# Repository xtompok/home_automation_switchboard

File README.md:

# home_automation_switchboard
Board fitting into wall switch, support for 1Wire, quadrature encoder, and much more. RS-485

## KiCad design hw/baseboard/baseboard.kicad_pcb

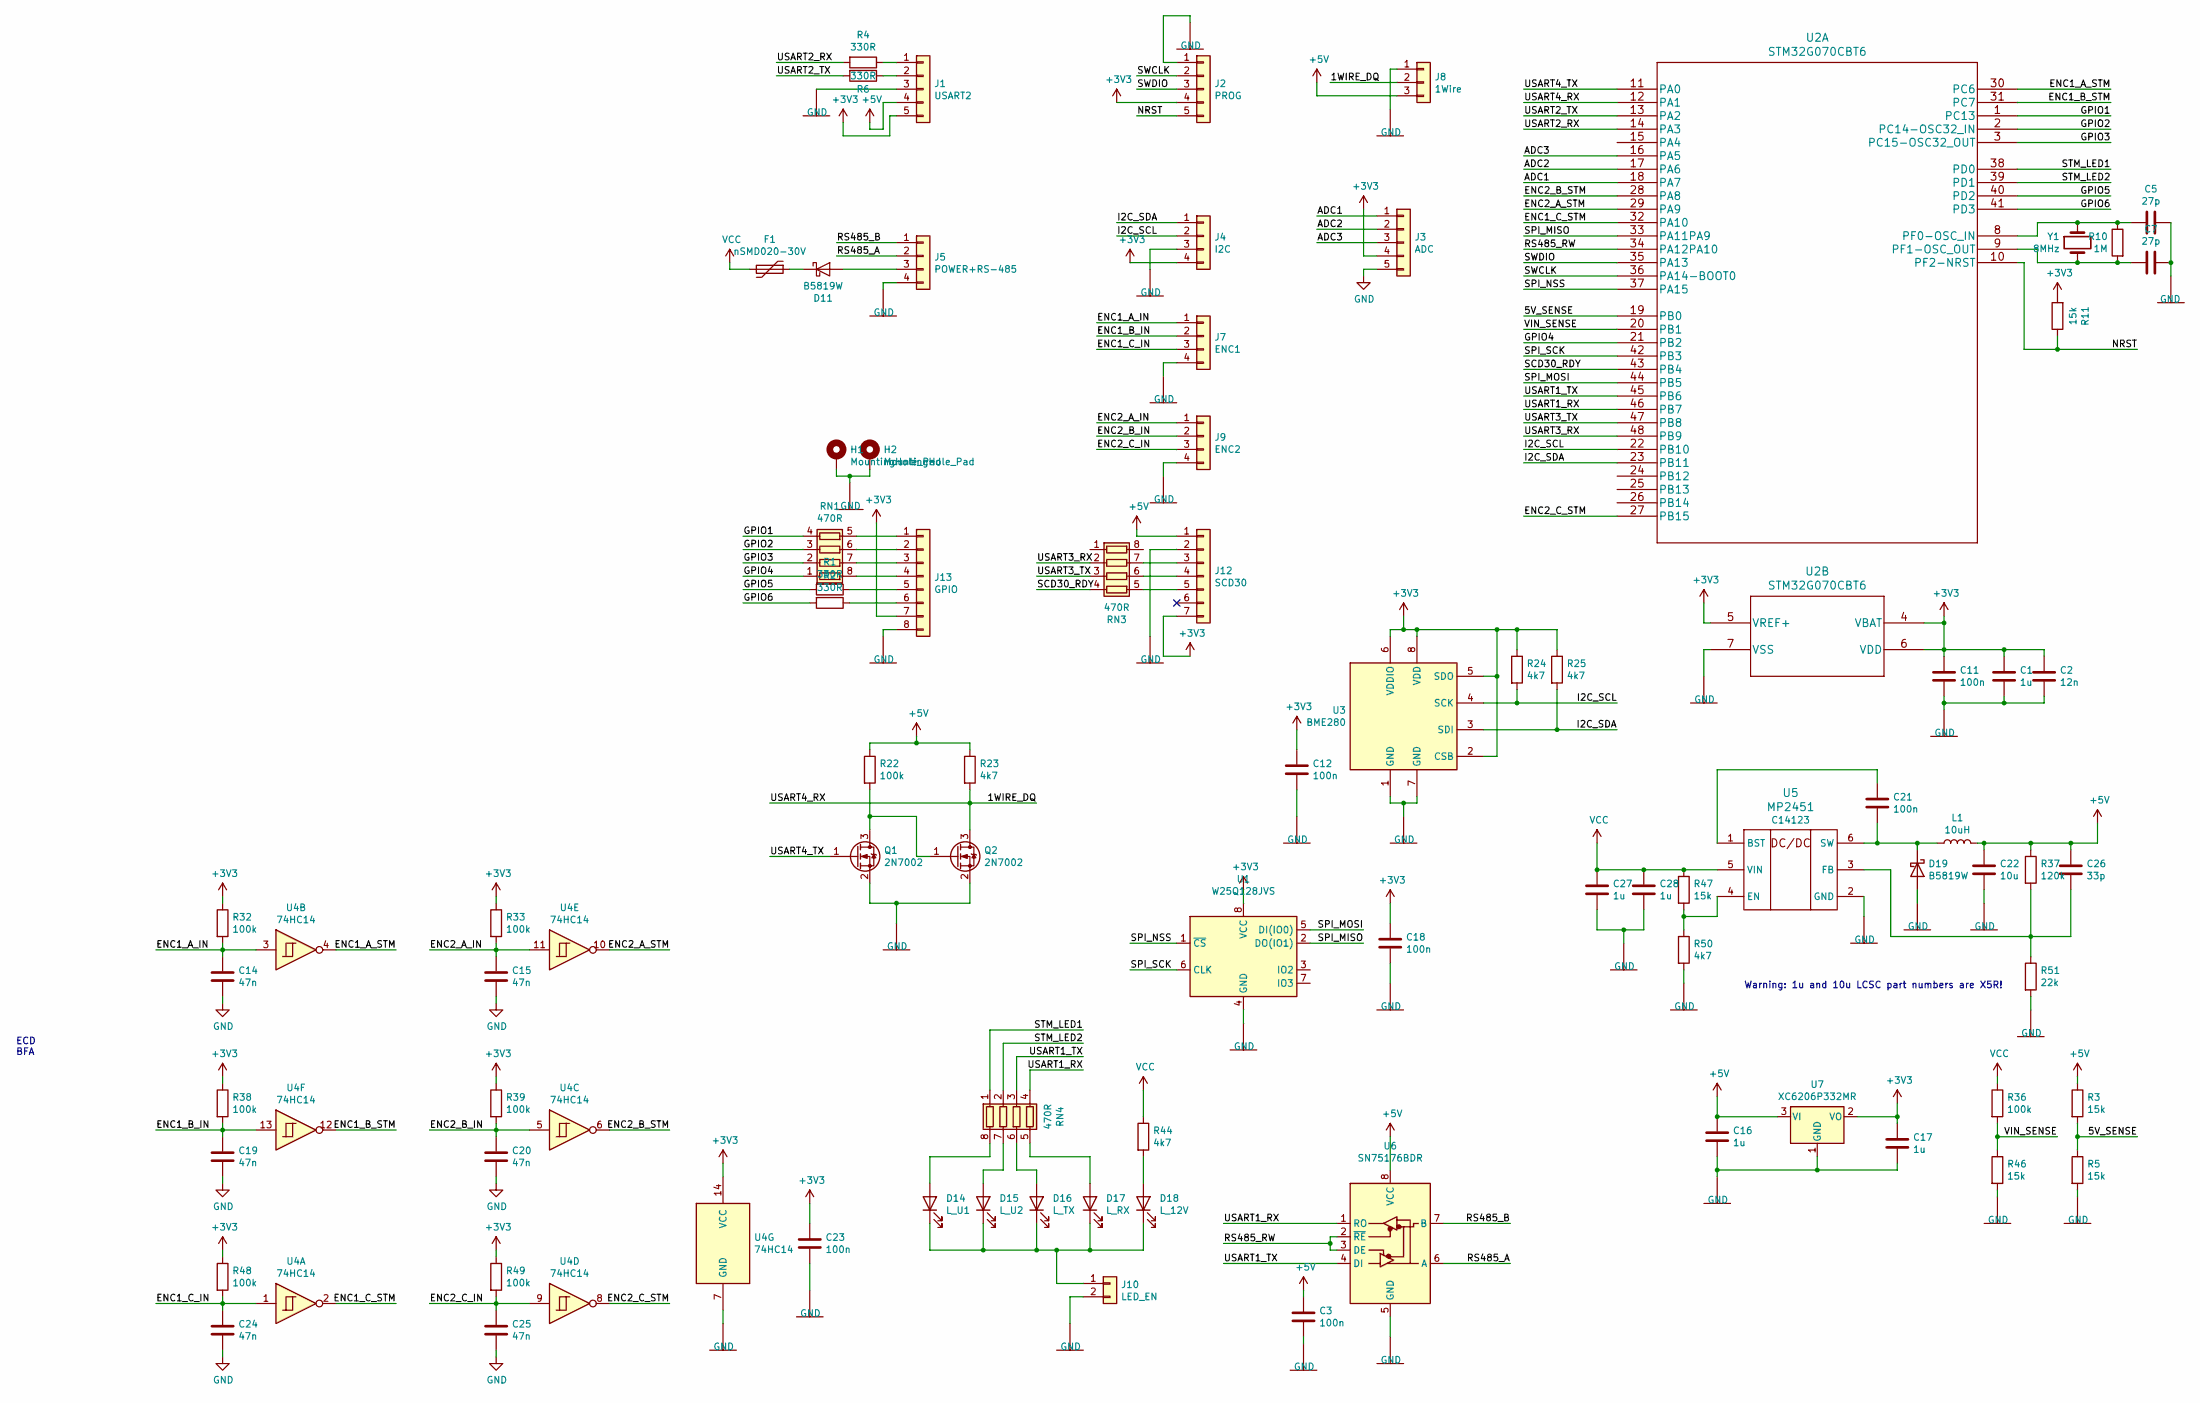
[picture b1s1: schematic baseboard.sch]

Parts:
C1: 1u; C_0603_1608Metric; LCSC C15849
C2: 12n; C_0603_1608Metric; LCSC C1593
C3, C12, C18, C21, C23: 100n; C_0603_1608Metric
C5: 27p; C_0603_1608Metric; LCSC C1656
C7: 27p; C_0603_1608Metric
C11: 100n; C_0603_1608Metric; LCSC C14663
C14: 47n; C_0603_1608Metric; LCSC C1622
C15, C19, C20, C24, C25: 47n; C_0603_1608Metric
C16, C17, C27, C28: 1u; C_0603_1608Metric
C22: 10u; C_0603_1608Metric; LCSC C19702
C26: 33p; C_0603_1608Metric; LCSC C1663
D11, D19: B5819W; D_SOD-123; LCSC C8598
D14: L_U1; LED_0603_1608Metric; LCSC C2286
D15: L_U2; LED_0603_1608Metric; LCSC C72043
D16: L_TX; LED_0603_1608Metric; LCSC C72038
D17: L_RX; LED_0603_1608Metric; LCSC C72043
D18: L_12V; LED_0603_1608Metric; LCSC C2286
F1: nSMD020-30V; Fuse_1206_3216Metric; LCSC C69680
H1, H2: MountingHole_Pad; MountingHole_3.2mm_M3_Pad_Via
J1: USART2; JST_PH_B5B-PH-K_1x05_P2.00mm_Vertical
J2: PROG; SIP-5
J3: ADC; JST_PH_B5B-PH-K_1x05_P2.00mm_Vertical
J4: I2C; JST_PH_B4B-PH-K_1x04_P2.00mm_Vertical
J5: POWER+RS-485; PTSA_1.5_4-3.5-Z-1985218
J7: ENC1; JST_PH_B4B-PH-K_1x04_P2.00mm_Vertical
J8: 1Wire; JST_PH_B3B-PH-K_1x03_P2.00mm_Vertical
J9: ENC2; JST_PH_B4B-PH-K_1x04_P2.00mm_Vertical
J10: LED_EN; PinHeader_1x02_P2.54mm_Vertical
J12: SCD30; PinHeader_1x07_P2.54mm_Vertical
J13: GPIO; JST_PH_B8B-PH-K_1x08_P2.00mm_Vertical
L1: 10uH; L_Abracon_ASPI-3012S; LCSC C96832
Q1: 2N7002; SOT-23; LCSC C8545
Q2: 2N7002; SOT-23
R1, R2, R6: 330R; R_0603_1608Metric
R3, R5, R46, R47: 15k; R_0603_1608Metric
R4: 330R; R_0603_1608Metric; LCSC C23138
R10: 1M; R_0603_1608Metric; LCSC C22935
R11: 15k; R_0603_1608Metric; LCSC C22809
R22: 100k; R_0603_1608Metric; LCSC C25803
R23: 4k7; R_0603_1608Metric; LCSC C23162
R24, R25, R44, R50: 4k7; R_0603_1608Metric
R32, R33, R36, R38, R39, R48, R49: 100k; R_0603_1608Metric
R37: 120k; R_0603_1608Metric; LCSC C25808
R51: 22k; R_0603_1608Metric; LCSC C31850
RN1, RN3, RN4: 470R; R_Array_Convex_4x0603; LCSC C25510
U1: W25Q128JVS; SOIC-8_5.23x5.23mm_P1.27mm; LCSC C97521
U2: STM32G070CBT6; LQFP-48_7x7mm_P0.5mm; LCSC C529338
U3: BME280; Bosch_LGA-8_2.5x2.5mm_P0.65mm_ClockwisePinNumbering; LCSC C92489
U4: 74HC14; SOIC-14_3.9x8.7mm_P1.27mm; LCSC C5605
U5: MP2451; SOT-23-6; LCSC C14123
U6: SN75176BDR; SOP-8_3.9x4.9mm_P1.27mm; LCSC C7063
U7: XC6206P332MR; SOT-23; LCSC C5446
Y1: 8MHz; Crystal_SMD_5032-2Pin_5.0x3.2mm; LCSC C115962

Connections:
+3V3: C1.1, C2.1, C11.1, C12.1, C17.1, C18.1, C23.1, J1.5, J2.4, J3.4, J4.4, J12.7, J13.7, R11.2, R24.1, R25.1, R32.1, R33.1, R38.1, R39.1, R48.1, R49.1, U1.8 (VCC), U2.4 (VBAT), U2.5 (VREF+), U2.6 (VDD), U3.2 (CSB), U3.5 (SDO), U3.6 (VDDIO), U3.8 (VDD), U4.14 (VCC), U7.2 (VO)
+5V: C3.1, C16.1, C22.1, C26.1, J1.4, J8.3, J12.1, L1.2, R3.1, R22.1, R23.1, R37.1, U6.8 (VCC), U7.3 (VI)
/1WIRE_DQ: J8.2, Q2.3 (D), R23.2, U2.12 (PA1)
/5V_SENSE: R3.2, R5.1, U2.19 (PB0)
/ADC1: J3.1, U2.18 (PA7)
/ADC2: J3.2, U2.17 (PA6)
/ADC3: J3.3, U2.16 (PA5)
/ENC1_A_IN: C14.1, J7.1, R32.2, U4.3
/ENC1_A_STM: U2.30 (PC6), U4.4
/ENC1_B_IN: C19.1, J7.2, R38.2, U4.13
/ENC1_B_STM: U2.31 (PC7), U4.12
/ENC1_C_IN: C24.1, J7.3, R48.2, U4.1
/ENC1_C_STM: U2.32 (PA10), U4.2
/ENC2_A_IN: C15.1, J9.1, R33.2, U4.11
/ENC2_A_STM: U2.29 (PA9), U4.10
/ENC2_B_IN: C20.1, J9.2, R39.2, U4.5
/ENC2_B_STM: U2.28 (PA8), U4.6
/ENC2_C_IN: C25.1, J9.3, R49.2, U4.9
/ENC2_C_STM: U2.27 (PB15), U4.8
/GPIO1: RN1.4 (R4.1), U2.1 (PC13)
/GPIO2: RN1.3 (R3.1), U2.2 (PC14-OSC32_IN)
/GPIO3: RN1.2 (R2.1), U2.3 (PC15-OSC32_OUT)
/GPIO4: RN1.1 (R1.1), U2.21 (PB2)
/GPIO5: R1.2, U2.40 (PD2)
/GPIO6: R2.2, U2.41 (PD3)
/I2C_SCL: J4.2, R24.2, U2.22 (PB10), U3.4 (SCK)
/I2C_SDA: J4.1, R25.2, U2.23 (PB11), U3.3 (SDI)
/NRST: J2.5, R11.1, U2.10 (PF2-NRST)
/RS485_A: J5.2, U6.6 (A)
/RS485_B: J5.1, U6.7 (B)
/RS485_RW: U2.34 (PA12PA10), U6.2 (~RE), U6.3 (DE)
/SCD30_RDY: RN3.4 (R4.1), U2.43 (PB4)
/SPI_MISO: U1.2 (DO(IO1)), U2.33 (PA11PA9)
/SPI_MOSI: U1.5 (DI(IO0)), U2.44 (PB5)
/SPI_NSS: U1.1 (~CS), U2.37 (PA15)
/SPI_SCK: U1.6 (CLK), U2.42 (PB3)
/STM_LED1: RN4.1 (R1.1), U2.38 (PD0)
/STM_LED2: RN4.2 (R2.1), U2.39 (PD1)
/SWCLK: J2.2, U2.36 (PA14-BOOT0)
/SWDIO: J2.3, U2.35 (PA13)
/USART1_RX: RN4.4 (R4.1), U2.46 (PB7), U6.1 (RO)
/USART1_TX: RN4.3 (R3.1), U2.45 (PB6), U6.4 (DI)
/USART2_RX: R4.2, U2.14 (PA3)
/USART2_TX: R6.2, U2.13 (PA2)
/USART3_RX: RN3.2 (R2.1), U2.48 (PB9)
/USART3_TX: RN3.3 (R3.1), U2.47 (PB8)
/USART4_TX: Q1.1 (G), U2.11 (PA0)
/VIN_SENSE: R36.2, R46.1, U2.20 (PB1)
GND: C1.2, C2.2, C3.2, C5.2, C7.2, C11.2, C12.2, C14.2, C15.2, C16.2, C17.2, C18.2, C19.2, C20.2, C22.2, C23.2, C24.2, C25.2, C27.2, C28.2, D19.2 (A), H1.1, H2.1, J1.3, J2.1, J3.5, J4.3, J5.4, J7.4, J8.1, J9.4, J10.2, J12.2, J13.8, Q1.2 (S), Q2.2 (S), R5.2, R46.2, R50.2, R51.2, U1.4 (GND), U2.7 (VSS), U3.1 (GND), U3.7 (GND), U4.7 (GND), U5.2 (GND), U6.5 (GND), U7.1 (GND)
unnamed: C5.1, R10.1, U2.8 (PF0-OSC_IN), Y1.1
unnamed: C7.1, R10.2, U2.9 (PF1-OSC_OUT), Y1.2
unnamed: C21.1, U5.1 (BST)
unnamed: C21.2, D19.1 (K), L1.1, U5.6 (SW)
unnamed: C26.2, R37.2, R51.1, U5.3 (FB)
unnamed: D11.1 (K), F1.1
unnamed: D11.2 (A), J5.3
unnamed: D14.1 (K), D15.1 (K), D16.1 (K), D17.1 (K), D18.1 (K), J10.1
unnamed: D14.2 (A), RN4.8 (R1.2)
unnamed: D15.2 (A), RN4.7 (R2.2)
unnamed: D16.2 (A), RN4.6 (R3.2)
unnamed: D17.2 (A), RN4.5 (R4.2)
unnamed: D18.2 (A), R44.2
unnamed: J1.1, R4.1
unnamed: J1.2, R6.1
unnamed: J12.3, RN3.7 (R2.2)
unnamed: J12.4, RN3.6 (R3.2)
unnamed: J12.5, RN3.5 (R4.2)
unnamed: J13.1, RN1.5 (R4.2)
unnamed: J13.2, RN1.6 (R3.2)
unnamed: J13.3, RN1.7 (R2.2)
unnamed: J13.4, RN1.8 (R1.2)
unnamed: J13.5, R1.1
unnamed: J13.6, R2.1
unnamed: Q1.3 (D), Q2.1 (G), R22.2
unnamed: R47.2, R50.1, U5.4 (EN)
VCC: C27.1, C28.1, F1.2, R36.1, R44.1, R47.1, U5.5 (VIN)

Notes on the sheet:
ECD BFA
Warning: 1u and 10u LCSC part numbers are X5R!

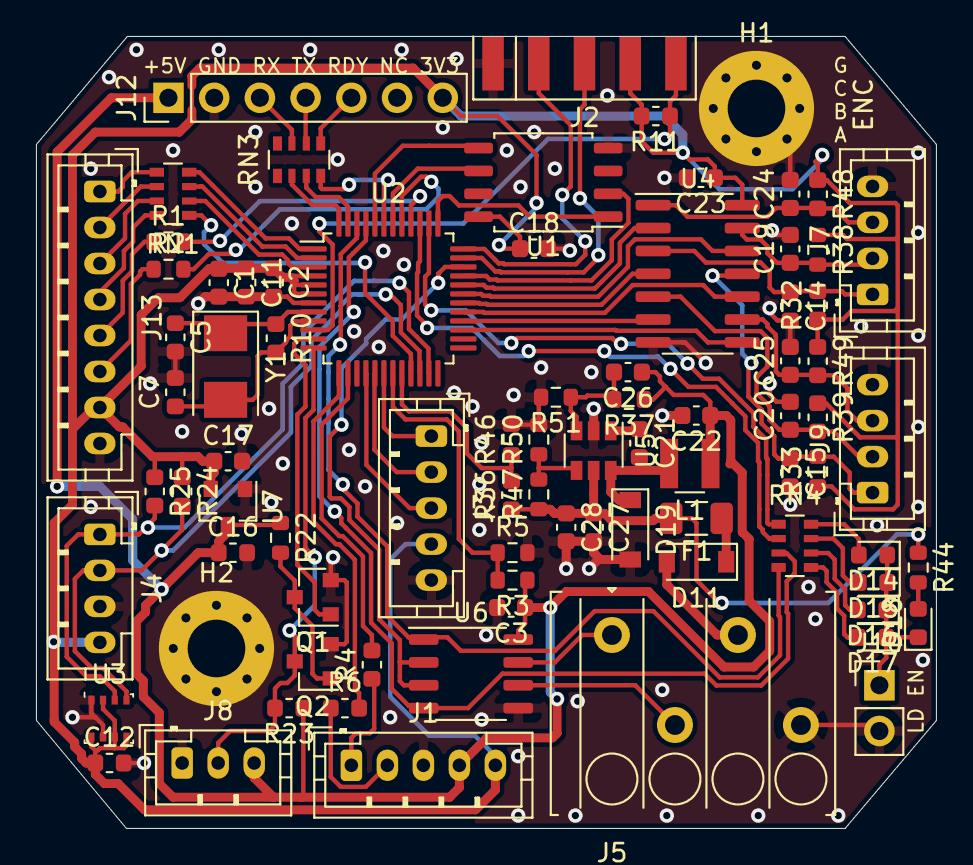
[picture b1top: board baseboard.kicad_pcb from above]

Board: 2 copper layers, 50.0 x 44.0 mm, 82 parts (0 on the bottom side), 76 nets.

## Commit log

2021-03-15 Added first prototype of the board.
2021-03-31 Testing fw.
